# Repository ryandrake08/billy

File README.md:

# Smart Mouth Billy Bass LLM jokester

Billy is a Big Mouth Billy Bass novelty toy converted into an **offline, LAN-only** voice
jokester. An ESP32-S3 inside the fish captures speech, drives the motors, and plays back
audio; a separate GPU box does speech-to-text, LLM inference, and text-to-speech. There is no
internet dependency anywhere in the pipeline.

The fish's' persona, conversation history, text cleanup, and configuraion all live on the
backend, in an business-logic "shim" application in front of the LLM. The fish just captures
audio, makes three HTTP calls per turn, plays the reply, and animates the mouth/head/tail in
sync with it.

## Architecture

```
        FISH (ESP32-S3)                                BACKEND (LAN)
  ┌──────────────────────────┐                  ┌───────────────────────────┐
  │ mic → capture utterance  │─── utterance ───▶│ whisper.cpp        :8081  │
  │                          │◀───── text ──────│                           │
  |                          |                  |                           |    ┌─────────────────┐
  │ text → shim              │────── text ─────▶│ shim (persona,     :8000  │──▶ | llama.cpp :8080 |
  │                          │◀─── response ────│  history, text cleaning)  │    └─────────────────┘
  │                          │                  │                           │
  │ sentence → TTS           │──── sentence ───▶│ Kokoro             :8880  │
  │                          │◀──── audio ──────│                           │
  │ amp + motors             │                  └───────────────────────────┘
  └──────────────────────────┘
```

Three calls per conversational turn:

| Call | Target | Request → Response |
|---|---|---|
| STT | whisper.cpp `:8081`, direct | `POST /inference` (multipart wav, `response_format=verbose_json`, `language=auto`) → `{"text", "detected_language", ...}` |
| brain | shim `:8000` | `POST /v1/respond` `{session, text, language}` → SSE stream of `{"sentence", "voice"}` |
| TTS | Kokoro `:8880`, direct | `POST /v1/audio/speech` `{model, input, voice}` → wav bytes |

STT and TTS are dumb audio↔text transforms called **directly**; only the brain hop goes through
the shim, which is a text-only service that never touches audio. The shim streams sentences as
the LLM generates them, so the caller can synthesize and play sentence 1 while sentence 2 is
still being generated — this pipelining is what keeps time-to-first-audio low.

There are three implementations of this protocol, and they should be indentical: the reference clients
`src/client/billy_cli.py` (Python) and `src/cli/` (C), and the ESP32 firmware
(`src/firmware/main/net.c`). The CLIs exist to document the protocol the firmware has to match —
the C one doubles as a check on how much of the firmware's own protocol code (WAV header,
hand-rolled JSON parsing, SSE reassembly) is genuinely ESP-IDF-independent and portable to a
host build; it turned out to be all of it.

## Repository layout

| Path | What |
|---|---|
| `board/` | Custom PCB for the fish's electronics (KiCad). |
| `src/firmware/` | ESP32-S3 firmware (C, ESP-IDF). |
| `src/shim/` | Backend application-logic layer (Python/FastAPI). |
| `src/client/` | CLI reference client (Python) — a mic+speaker stand-in for the fish. |
| `src/cli/` | CLI reference client (C) — built against libcurl/PortAudio/soxr. |
| `src/tests/` | End-to-end integration test for the multi-language STT→shim→LLM pipeline. |

---

## `board/` — Custom PCB

KiCad project at `board/billy/`. Replaces the toy's stock control board with a single board
carrying the ESP32-S3, motor drivers, amp, buck regulator, and power-input protection,
designed to fit inside the original toy's chassis (~70×50mm).

| Part | Role |
|---|---|
| ESP32-S3-WROOM-1-N4R2 | Controller — WiFi, dual I²S, deep sleep |
| TDK ICS-43434 (I²S MEMS mic) | Microphone — mounted as a separate satellite board, off the main PCB, for acoustic placement |
| MAX98357A (I²S class-D amp) | Speaker drive |
| 2× TI DRV8833 (dual H-bridge) | 3 motor channels — mouth, head, tail (all spring-return, unidirectional) |
| DIODES AP63203 buck | 6V → 3.3V logic/audio rail |
| AOS AO3401A / AO3400A FETs (battery reverse-polarity protection, USB/motor-rail isolation pass FET, status LED + photocell/Vmotor-sense divider gating) | Power-input protection and deep-sleep peripheral gating |
| Analog Devices LTC4412 | Ideal-diode controller — motor rail vs. USB arbitration into the buck |
| MCC B5817W Schottky | Passive ideal diode — USB VBUS into the buck |
| 2× 5A slow-blow fuses | Battery and DC-jack input protection |

The KiCad schematic and PCB are authoritative for hardware connectivity and layout. Firmware
`board.h` mirrors the schematic's GPIO assignments and must stay synchronized with it.

**Workflow:**
```bash
open board/billy/billy.kicad_pro
kicad-cli sch erc --format json --severity-all -o erc.json board/billy/billy.kicad_sch
kicad-cli pcb drc --format json --severity-all --schematic-parity -o drc.json board/billy/billy.kicad_pcb
```

---

## `src/firmware/` — ESP32-S3 firmware

Captures speech, calls the backend for STT → LLM → TTS, plays the reply, and drives the
mouth/head/tail motors in sync with it. Targets `esp32s3` (tested with ESP-IDF v6.0.2).

### Layering

| Layer | Files | Responsibility |
|---|---|---|
| app | `main.c` | `app_main()` wires everything together; `runloop_task` runs the `IDLE→ACTIVATE→LISTEN→THINK→SPEAK→IDLE` state machine. |
| transport | `net.c/.h` | The fish↔backend contract described above — STT direct, brain hop through the shim, TTS direct. |
| device | `audio.c/.h`, `motors.c/.h`, `activation.c/.h`, `peripherals.c/.h` | Fish-specific setup and algorithms built on the HAL: I²S mic/amp + mouth lip-sync envelope; 2× DRV8833 motor choreography with `nFAULT` telemetry and deferred Vmotor capture; button/mode-switch/wake-word activation + deep sleep; WS2812 status LED + photocell/Vmotor-sense reads, all gated by one shared enable line. |
| HAL | `hal.c/.h` | Generic, pin-parameterized primitives (GPIO, ADC1, LED strip, PWM, I²S, deep sleep) with no fish-specific naming and no `board.h` dependency of its own. |

`board.h` is the firmware representation of the schematic pin map. `components/wakeword` is the on-device
wake-word detector (TensorFlow Lite Micro, ported from ESPHome's `micro_wake_word` component). See its own
`models/ATTRIBUTION.md` for training provenance.

### Build

```bash
source ~/.espressif/tools/activate_idf_v6.0.2.sh
cd src/firmware
export WIFI_SSID="your-2.4GHz-ssid" WIFI_PASSWORD="your-password" BACKEND_HOST="your-backend-hostname-or-ip"
idf.py set-target esp32s3      # once
idf.py build
idf.py -p <port> flash monitor
```
WiFi credentials and the backend host are build-environment variables injected as compile
definitions (`main/CMakeLists.txt`). Changing one needs `idf.py reconfigure`. `./clean.sh`
removes all generated build state.

### Debug

Step-debug with breakpoints over the S3's native USB-Serial-JTAG:
```bash
openocd -f board/esp32s3-builtin.cfg    # terminal 1
idf.py -p <port> gdb                    # terminal 2
```
The DevKitC-1 has two USB ports — flashing uses the UART/CP2102 port; OpenOCD needs the
separate native-USB port instead. The production board has a USB port and a three pin
header (TTL level) to one of the ESP32's built-in UARTs. Only use a USB-to-UART cable that
uses 3.3V with this header! In addition to the direct-to-UART header, the production board
has a two pin header for firmware flashing. Jumping the header during a reset causes the chip
to enter UART download (flashing) mode instead of booting normally from flash memory.
The UART/FLASH headers are intended to be a backup in case flashing over USB fails, and the
header can be left unpopulated if unused.

### Runtime behavior

`runloop_task` starts immediately on boot and idles waiting for activation; it does not block
on WiFi or the backend being reachable. Activation depends on the mode switch: **button mode**
(press-to-talk, deep-sleeps between turns) or **wake-word mode** (mic stays live, listens for
"hey billy"; a button press also works as a manual override). Flipping the switch mid-wait
preempts immediately. Runtime-tunable constants (VAD thresholds, mouth/tail timing, and HTTP
timeouts) are fetched from the shim's `/v1/config` every loop cycle rather than compiled
in, with compiled-in fallbacks if the shim is unreachable. Each capture's VAD threshold adapts
to the room's ambient noise level, measured during the pre-capture drain window, so a noisy
room still reads as silence once the user stops talking. The DRV8833 `nFAULT` line is logged but
does not gate motor commands because it asserts unreliably on the board; the drivers' independent
silicon overcurrent, thermal, and undervoltage protection remains active.

---

## `src/shim/` — backend application-logic layer

The brain layer in front of `llama.cpp`. Holds the application logic that has to live off the
fish for it to stay a thin client:

- **persona** / system prompt — edit `text.py`, reload;
- **conversation history / session state** — kept server-side, keyed by session id;
- **model quirks** — the `enable_thinking` request flag and `<think>`-block stripping;
- **markdown/emoji scrubbing** — the LLM still emits stray formatting that TTS would mangle;
- **sentence splitting + streaming** — emits clean sentences as they're ready so the caller can
  pipeline TTS for low first-audio latency;
- **per-language voice routing** (`text.py`'s `LANGUAGE_VOICES`) — English (`am_onyx`) plus
  Spanish, Brazilian Portuguese, Mandarin, Japanese, Hindi, and Italian, picked from the caller's
  detected language and overridable per sentence for an explicit switch mid-reply;
- **runtime firmware config** (`fish_config.py`) — tunable firmware constants served over
  `GET /v1/config`, so they can be retuned without a reflash.

### Protocol

| Call | Request | Response |
|---|---|---|
| `POST /v1/respond` | `{"session": "default", "text": "<user utterance>", "language": "english"}` | `text/event-stream`: one `data: {"sentence": ..., "voice": ...}` per spoken sentence, then `data: [DONE]` |
| `POST /v1/reset` | `{"session": "default"}` | `{"reset": "<session>"}` |
| `GET /v1/config` | — | Runtime firmware-tunable constants |
| `GET /health` | — | `{status, llm_url, llm_model, llm_reachable, sessions}` |

### Run

```bash
cd src/shim
python3 -m venv .venv && .venv/bin/pip install -r requirements.txt
.venv/bin/uvicorn billy_shim:app --host 0.0.0.0 --port 8000
```
Config via env: `BILLY_LLM_URL` (default `http://localhost:8080`), `BILLY_LLM_MODEL` (default
`Qwen3.5-9B`). Tests use plain asserts rather than pytest:

```bash
.venv/bin/python test_text.py
.venv/bin/python test_config.py
.venv/bin/python test_session.py
```

### Deploy

Shim program can live anywhere. Recommend using your OS's init system to start and manage it.

---

## `src/client/` — CLI reference client (Python)

A command-line stand-in for the fish: drives the full backend pipeline (record → STT → shim →
TTS → play) from any host with a mic and speaker.

### Run

```bash
cd src/client
python3 -m venv .venv && . .venv/bin/activate && pip install -r requirements.txt
./billy_cli.py --host <backend-host>     # ports 8000/8081/8880 derived from host
```
Press **Enter** to start talking, speak, press **Enter** to stop. `Ctrl-C` quits.

`--voice <kokoro-voice>` overrides the voice for the whole session (browse the list at
`http://<backend-host>:8880/web`); otherwise each sentence uses the shim's own per-sentence
choice. `--session <id>` sets the shim conversation id; `--shim-url`/`--stt-url`/`--tts-url`
override individual endpoints. Uses the system default audio devices.

`--input-wav <path>` skips the mic entirely: runs one turn on that WAV file's bytes (16 kHz mono,
same as the mic path itself records) and exits — for testing the same utterance repeatedly
without re-recording it by hand each time.

Each turn prints various latency measurements.

---

## `src/cli/` — CLI reference client (C)

A second, independent reference client for the same contract — same record → STT → shim → TTS →
play pipeline as the Python client, same flags, same latency breakdown, but built as a plain C
binary via CMake instead of a Python venv.

External dependencies (none of this is vendored): `libcurl` (HTTP, mirrors `httpx`), `portaudio`
(mic/speaker I/O, mirrors `sounddevice`), `soxr` (output resampling, same library the Python
`soxr` package binds to). On macOS via MacPorts: `port install curl portaudio soxr`.

### Build & run

```bash
cd src/cli
cmake -S . -B build && cmake --build build
./build/billy_cli --host <backend-host>     # ports 8000/8081/8880 derived from host
```
Press **Enter** to start talking, speak, press **Enter** to stop. `Ctrl-C` quits, same as the
Python client.

Same `--voice`/`--session`/`--shim-url`/`--stt-url`/`--tts-url` flags as the Python client, same
system-default audio devices. TTS audio is resampled to the output device's native rate in
software (soxr, `SOXR_HQ` quality).

---

## `src/tests/` — end-to-end integration test

Exercises the  STT→shim→LLM chain for every supported language. For each language, a
"golden" WAV asking Billy to repeat a fixed phrase is transcribed by real whisper.cpp, then sent
to a shim, checking the reply comes back in the right voice and language.

```bash
cd src/tests
python3 -m venv .venv && .venv/bin/pip install -r requirements.txt
./.venv/bin/python test_language_integration.py     # needs src/shim/.venv already set up
```

The golden WAVs in `golden/` are gitignored: `generate_golden.py` makes them with Microsoft's
free `edge-tts`. The test does this itself the first time golden/ is missing a file.

---

## Backend engines

Three off-the-shelf inference engines run on the backend GPU host alongside the shim, all under
systemd (`Restart=always`, enabled at boot):

| Service | Port | Model | GPU |
|---|---|---|---|
| llama.cpp | 8080 | Qwen3.5-9B, Q8_0, non-thinking mode | yes |
| whisper.cpp | 8081 | `large-v3` | yes |
| Kokoro (Kokoro-FastAPI) | 8880 | `am_onyx` + 6 other language voices (see `src/shim/`) | yes |

All three plus the shim are expected to fit resident in ~14GB of VRAM.

---

## License

Source code and documentation are licensed under [Apache License 2.0](LICENSE). The
trained wake-word model `src/firmware/components/wakeword/models/hey_billy.tflite` is
explicitly excluded; see [NOTICE](NOTICE) and its
[`ATTRIBUTION.md`](src/firmware/components/wakeword/models/ATTRIBUTION.md).

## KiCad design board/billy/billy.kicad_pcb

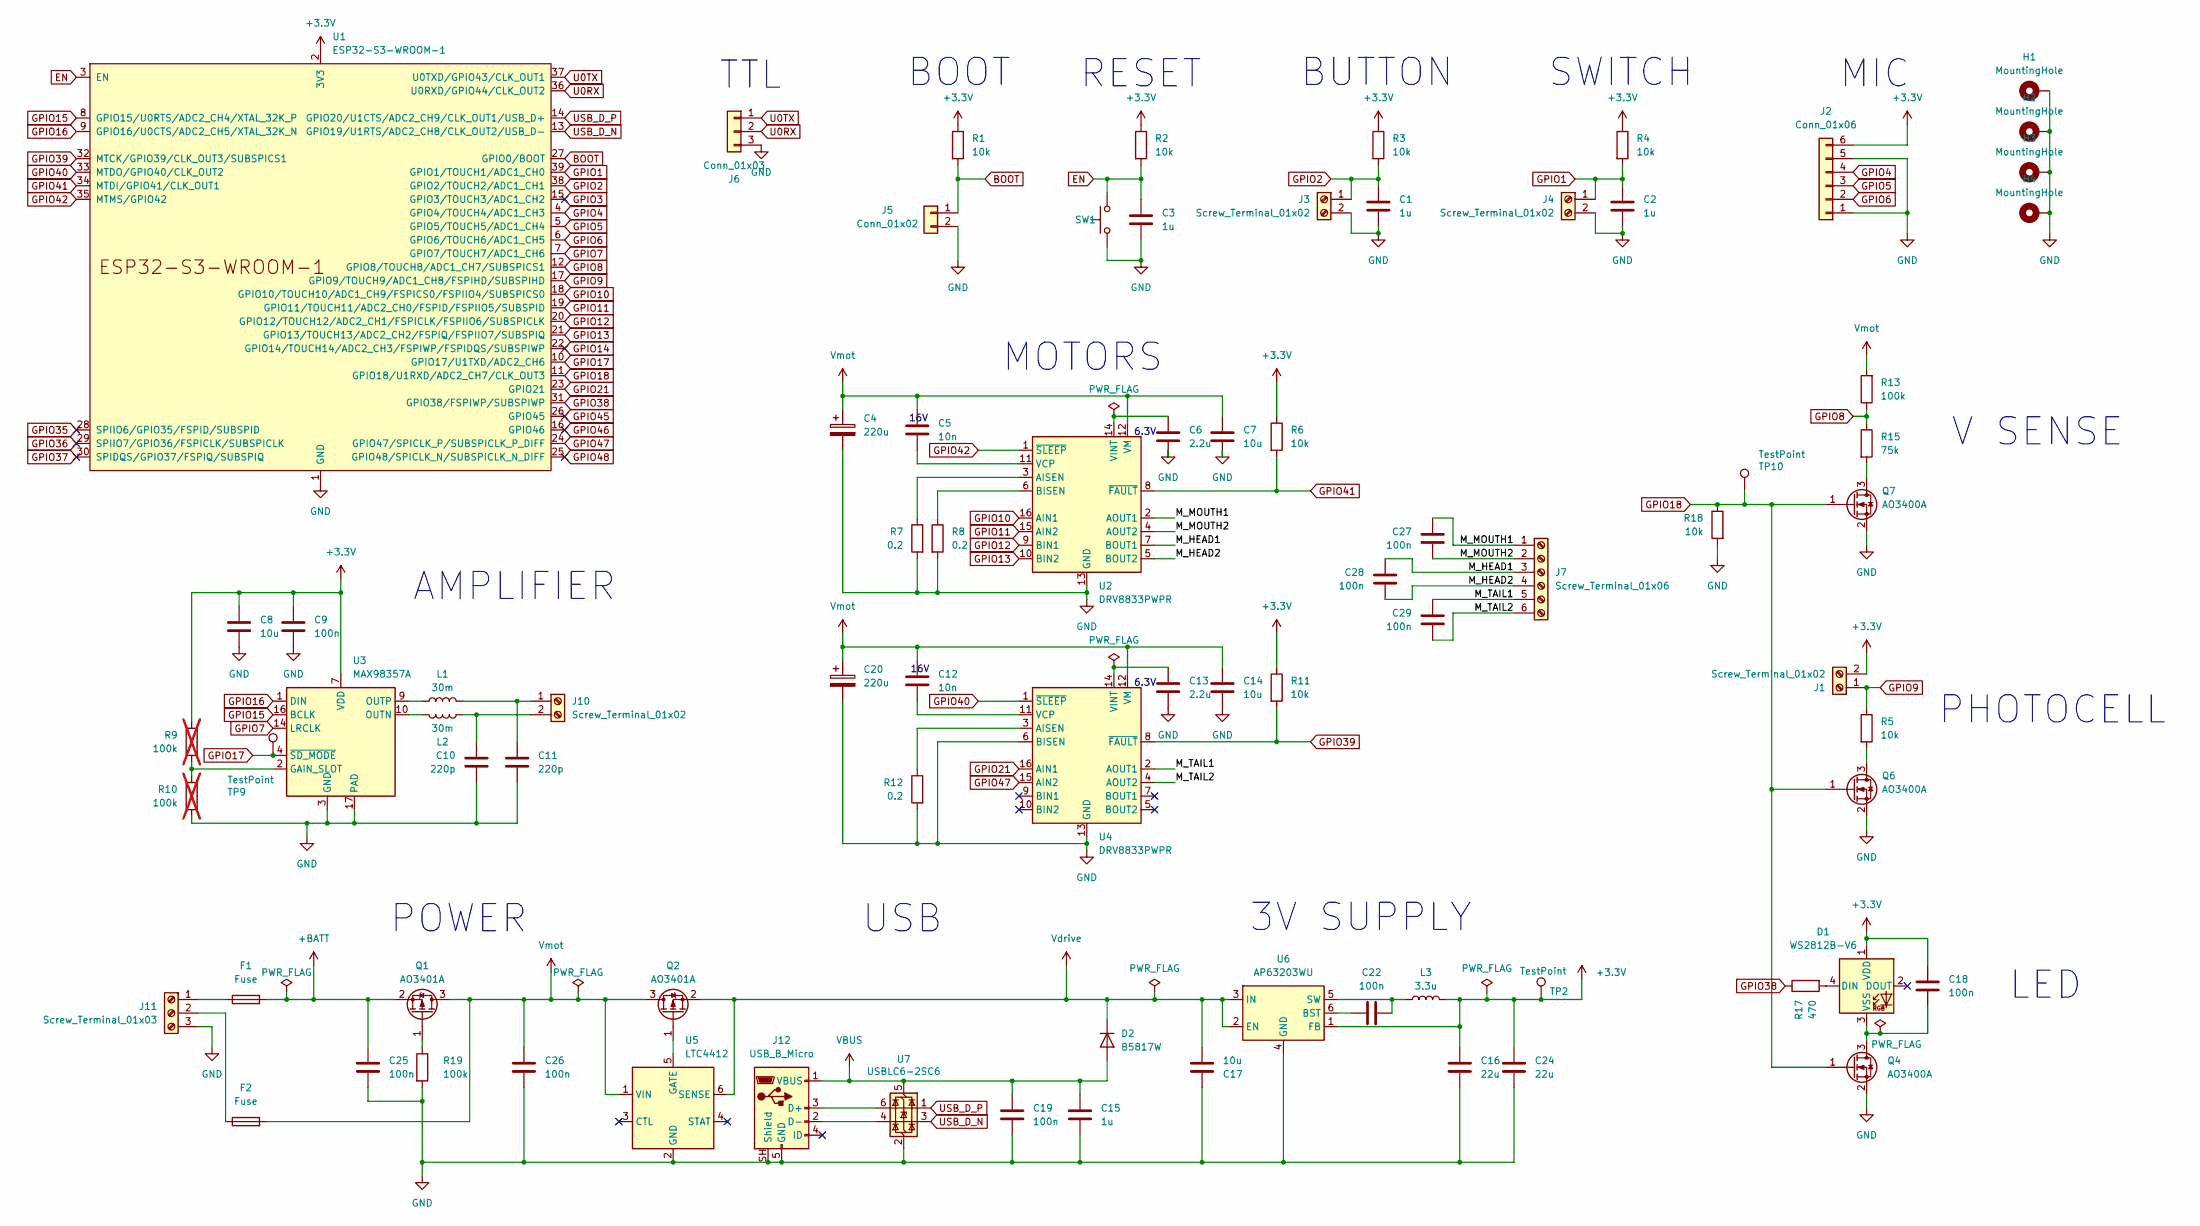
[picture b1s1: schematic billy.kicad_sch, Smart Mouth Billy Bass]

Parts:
C1, C2, C3, C15: 1u; C_0603_1608Metric; Mouser Part 187-CL10B105KP8NNNC; LCSC Part C52923
C4, C20: 220u; CP_Elec_6.3x5.9; Mouser Part 667-EEE-FT1C221AP; LCSC Part C401766
C5, C12: 10n; C_0603_1608Metric; Mouser Part 187-CL05B103KB5NNNC; LCSC Part C15195
C6, C13: 2.2u; C_0603_1608Metric; Mouser Part 187-CL10A225KP8NNNC; LCSC Part C23630
C7, C8, C14: 10u; C_0603_1608Metric; Mouser Part 187-CL10A106KP8NNND; LCSC Part C19702
C9, C18, C19, C22, C25, C26, C27, C28, C29: 100n; C_0603_1608Metric; Mouser Part 187-CL10B104JB8NNNC; LCSC Part C1525
C10, C11: 220p; C_0603_1608Metric; Mouser Part 187-CL10B221KB8NNNC; LCSC Part C1530
C16, C24: 22u; C_1206_3216Metric; Mouser Part 187-CL31B226KPHNNNE; LCSC Part C45783
C17: 10u; C_1206_3216Metric; Mouser Part 187-CL31B106KLHNNNE; LCSC Part C45783
D1: WS2812B-V6; LED_WS2812B_PLCC4_5.0x5.0mm_P3.2mm; LCSC Part C52941391
D2: B5817W; D_SOD-323; Mouser Part 833-B5817W-TP; DigiKey Part B5817WS-TPMSCT-ND
F1, F2: Fuse; Fuse_Littelfuse-NANO2-451_453; Mouser Part 576-0454005.MR; LCSC Part C206917
H1, H2, H3, H4: MountingHole; MountingHole_3.2mm_M3_ISO7380_Pad
J1, J3, J4, J10: Screw_Terminal_01x02; TerminalBlock_Xinya_XY308-2.54-2P_1x02_P2.54mm_Horizontal; Mouser Part 651-1725656; LCSC Part C918120
J2: Conn_01x06; PinHeader_1x06_P2.54mm_Horizontal; Mouser Part 710-61300611021; LCSC Part C492414
J5: Conn_01x02; PinHeader_1x02_P2.54mm_Vertical; Mouser Part 710-61300211121; LCSC Part C492401
J6: Conn_01x03; PinHeader_1x03_P2.54mm_Vertical; Mouser Part 710-61300311121; LCSC Part C2937625
J7: Screw_Terminal_01x06; TerminalBlock_Xinya_XY308-2.54-6P_1x06_P2.54mm_Horizontal; Mouser Part 651-1725698; LCSC Part C918124
J11: Screw_Terminal_01x03; TerminalBlock_Xinya_XY308-2.54-3P_1x03_P2.54mm_Horizontal; Mouser Part 651-1725669; LCSC Part C918121
J12: USB_B_Micro; USB_Micro-B_Amphenol_10118194-0001LF_Horizontal; Mouser Part 649-10118194-0001LF; LCSC Part C132563
L1, L2: 30m; L_0603_1608Metric; Mouser Part 81-BLM18KG121TN1D; LCSC Part C14709
L3: 3.3u; L_APV_ANR4030; Mouser Part 739-TYA40203R3M-10; DigiKey Part 240-TYA40203R3M-10CT-ND
Q1, Q2: AO3401A; SOT-23; LCSC Part C15127
Q4, Q6, Q7: AO3400A; SOT-23; LCSC Part C20917
R1, R2, R3, R4, R5, R6, R11, R18: 10k; R_0603_1608Metric; Mouser Part 708-RMCF0603FT10K0; LCSC Part C25804
R7, R8, R12: 0.2; R_1206_3216Metric; Mouser Part 708-CSR1206FKR200; LCSC Part C473037
R9, R10: 100k; R_0603_1608Metric; Mouser Part 708-RMCF0603FT100K; LCSC Part C25803; not fitted
R13, R19: 100k; R_0603_1608Metric; Mouser Part 708-RMCF0603FT100K; LCSC Part C25803
R15: 75k; R_0603_1608Metric; Mouser Part 708-RMCF0603FT75K0; DigiKey Part RMCF0603FT75K0CT-ND
R17: 470; R_0603_1608Metric; Mouser Part 708-RMCF0603FT470R; LCSC Part C23179
SW1: TS-1088-AR02016; SW_SPST_TS-1088-xR020; Mouser Part 688-SKRKAG; LCSC Part C720477
TP2, TP9, TP10: TestPoint; TestPoint_Pad_1.0x1.0mm
U1: ESP32-S3-WROOM-1; Mouser Part 356-ESP32S3WROM1N4R2; LCSC Part C2913203
U2, U4: DRV8833PWPR; HTSSOP-16-1EP_4.4x5mm_P0.65mm_EP3.4x5mm; Mouser Part 595-DRV8833PWPR; LCSC Part C50506
U3: MAX98357A; TQFN-16-1EP_3x3mm_P0.5mm_EP1.23x1.23mm; Mouser Part 700-MAX98357AETE+T; LCSC Part C910544
U5: LTC4412; TSOT-23-6; Mouser Part 584-LTC4412ES6TRMPBF; DigiKey Part 505-LTC4412ES6#TRMPBFCT-ND
U6: AP63203WU; TSOT-23-6; Mouser Part 621-AP63203QWU-7; LCSC Part C780769
U7: USBLC6-2SC6; SOT-23-6; Mouser Part 511-USBLC6-2SC6; LCSC Part C7519

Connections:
+3.3V: C8.1, C9.1, C16.1, C18.1, C24.1, D1.1 (VDD), J1.2, J2.6, L3.2, R1.1, R2.1, R3.1, R4.1, R6.1, R9.1, R11.1, TP2.1 (1_1), U1.2 (3V3), U3.7 (VDD), U3.8 (VDD), U6.1 (FB)
+BATT: C25.1, F1.2, Q1.2 (S)
/M_HEAD1: C28.1, J7.3, U2.7 (BOUT1)
/M_HEAD2: C28.2, J7.4, U2.5 (BOUT2)
/M_MOUTH1: C27.1, J7.1, U2.2 (AOUT1)
/M_MOUTH2: C27.2, J7.2, U2.4 (AOUT2)
/M_TAIL1: C29.2, J7.5, U4.2 (AOUT1)
/M_TAIL2: C29.1, J7.6, U4.4 (AOUT2)
BOOT: J5.1, R1.2, U1.27 (GPIO0/BOOT)
EN: C3.1, R2.2, SW1.2, U1.3 (EN)
GND: C1.2, C2.2, C3.2, C4.2, C6.2, C7.2, C8.2, C9.2, C10.2, C11.2, C13.2, C14.2, C15.2, C16.2, C17.2, C19.2, C20.2, C24.2, C25.2, C26.2, H1.1 (1_1), H2.1 (1_1), H3.1 (1_1), H4.1 (1_1), J2.1, J2.5, J3.2, J4.2, J5.2, J6.3, J11.3, J12.5 (GND), J12.SH (Shield), Q4.2 (S), Q6.2 (S), Q7.2 (S), R7.2, R8.2, R10.2, R12.2, R18.2, R19.2, SW1.1, U1.1 (GND), U1.40 (GND), U1.41 (GND), U2.13 (GND), U2.17 (GND), U3.3 (GND), U3.11 (GND), U3.15 (GND), U3.17 (PAD), U4.6 (BISEN), U4.13 (GND), U4.17 (GND), U5.2 (GND), U6.4 (GND), U7.2 (GND)
GPIO1: C2.1, J4.1, R4.2, U1.39 (GPIO1/TOUCH1/ADC1_CH0)
GPIO2: C1.1, J3.1, R3.2, U1.38 (GPIO2/TOUCH2/ADC1_CH1)
GPIO3: U1.15 (GPIO3/TOUCH3/ADC1_CH2)
GPIO4: J2.4, U1.4 (GPIO4/TOUCH4/ADC1_CH3)
GPIO5: J2.3, U1.5 (GPIO5/TOUCH5/ADC1_CH4)
GPIO6: J2.2, U1.6 (GPIO6/TOUCH6/ADC1_CH5)
GPIO7: U1.7 (GPIO7/TOUCH7/ADC1_CH6), U3.14 (LRCLK)
GPIO8: R13.1, R15.1, U1.12 (GPIO8/TOUCH8/ADC1_CH7/SUBSPICS1)
GPIO9: J1.1, R5.1, U1.17 (GPIO9/TOUCH9/ADC1_CH8/FSPIHD/SUBSPIHD)
GPIO10: U1.18 (GPIO10/TOUCH10/ADC1_CH9/FSPICS0/FSPIIO4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), U2.16 (AIN1)
GPIO11: U1.19 (GPIO11/TOUCH11/ADC2_CH0/FSPID/FSPIIO5/S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), U2.15 (AIN2)
GPIO12: U1.20 (GPIO12/TOUCH12/ADC2_CH1/FSPICLK/FSPIIO6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), U2.9 (BIN1)
GPIO13: U1.21 (GPIO13/TOUCH13/ADC2_CH2/FSPIQ/FSPIIO7/S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), U2.10 (BIN2)
GPIO14: U1.22 (GPIO14/TOUCH14/ADC2_CH3/FSPIWP/FSPIDQS/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)
GPIO15: U1.8 (GPIO15/U0RTS/ADC2_CH4/XTAL_32K_P), U3.16 (BCLK)
GPIO16: U1.9 (GPIO16/U0CTS/ADC2_CH5/XTAL_32K_N), U3.1 (DIN)
GPIO17: TP9.1 (1_1), U1.10 (GPIO17/U1TXD/ADC2_CH6), U3.4 (~SD_MODE)
GPIO18: Q4.1 (G), Q6.1 (G), Q7.1 (G), R18.1, TP10.1 (1_1), U1.11 (GPIO18/U1RXD/ADC2_CH7/CLK_OUT3)
GPIO21: U1.23 (GPIO21), U4.16 (AIN1)
GPIO35: U1.28 (SPIIO6/GPIO35/FSPID/SUBSPID)
GPIO36: U1.29 (SPIIO7/GPIO36/FSPICLK/SUBSPICLK)
GPIO37: U1.30 (SPIDQS/GPIO37/FSPIQ/SUBSPIQ)
GPIO38: R17.1, U1.31 (GPIO38/FSPIWP/SUBSPIWP)
GPIO39: R11.2, U1.32 (MTCK/GPIO39/CLK_OUT3/SUBSPICS1), U4.8 (~FAULT)
GPIO40: U1.33 (MTDO/GPIO40/CLK_OUT2), U4.1 (~SLEEP)
GPIO41: R6.2, U1.34 (MTDI/GPIO41/CLK_OUT1), U2.8 (~FAULT)
GPIO42: U1.35 (MTMS/GPIO42), U2.1 (~SLEEP)
GPIO45: U1.26 (GPIO45)
GPIO46: U1.16 (GPIO46)
GPIO47: U1.24 (GPIO47/SPICLK_P/SUBSPICLK_P_DIFF), U4.15 (AIN2)
GPIO48: U1.25 (GPIO48/SPICLK_N/SUBSPICLK_N_DIFF)
unnamed: D1.4 (DIN), R17.2
unnamed: C18.2, D1.3 (VSS), Q4.3 (D)
unnamed: C11.1, J10.1, L1.2
unnamed: C10.1, J10.2, L2.1
unnamed: F1.1, J11.1
unnamed: F2.1, J11.2
unnamed: J12.3 (D+), U7.6 (I/O1)
unnamed: J12.2 (D-), U7.4 (I/O2)
unnamed: Q1.1 (G), R19.1
unnamed: Q2.1 (G), U5.5 (GATE)
unnamed: Q6.3 (D), R5.2
unnamed: Q7.3 (D), R15.2
unnamed: R7.1, U2.3 (AISEN)
unnamed: R8.1, U2.6 (BISEN)
unnamed: C5.2, U2.11 (VCP)
unnamed: C6.1, U2.14 (VINT)
unnamed: R9.2, R10.1, U3.2 (GAIN_SLOT)
unnamed: L2.2, U3.10 (OUTN)
unnamed: L1.1, U3.9 (OUTP)
unnamed: R12.1, U4.3 (AISEN)
unnamed: C12.2, U4.11 (VCP)
unnamed: C13.1, U4.14 (VINT)
unnamed: C22.1, U6.6 (BST)
unnamed: C22.2, L3.1, U6.5 (SW)
U0RX: J6.2, U1.36 (U0RXD/GPIO44/CLK_OUT2)
U0TX: J6.1, U1.37 (U0TXD/GPIO43/CLK_OUT1)
USB_D_N: U1.13 (GPIO19/U1RTS/ADC2_CH8/CLK_OUT2/USB_D-), U7.3 (I/O2)
USB_D_P: U1.14 (GPIO20/U1CTS/ADC2_CH9/CLK_OUT1/USB_D+), U7.1 (I/O1)
VBUS: C15.1, C19.1, D2.2 (A), J12.1 (VBUS), U7.5 (VBUS)
Vdrive: C17.1, D2.1 (K), Q2.2 (S), U5.6 (SENSE), U6.2 (EN), U6.3 (IN)
Vmot: C4.1, C5.1, C7.1, C12.1, C14.1, C20.1, C26.1, F2.2, Q1.3 (D), Q2.3 (D), R13.2, U2.12 (VM), U4.12 (VM), U5.1 (VIN)

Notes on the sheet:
SWITCH
16V
LED
AMPLIFIER
3V SUPPLY
USB
TTL
BOOT
RESET
MIC
POWER
PHOTOCELL
V SENSE
BUTTON
6.3V
MOTORS

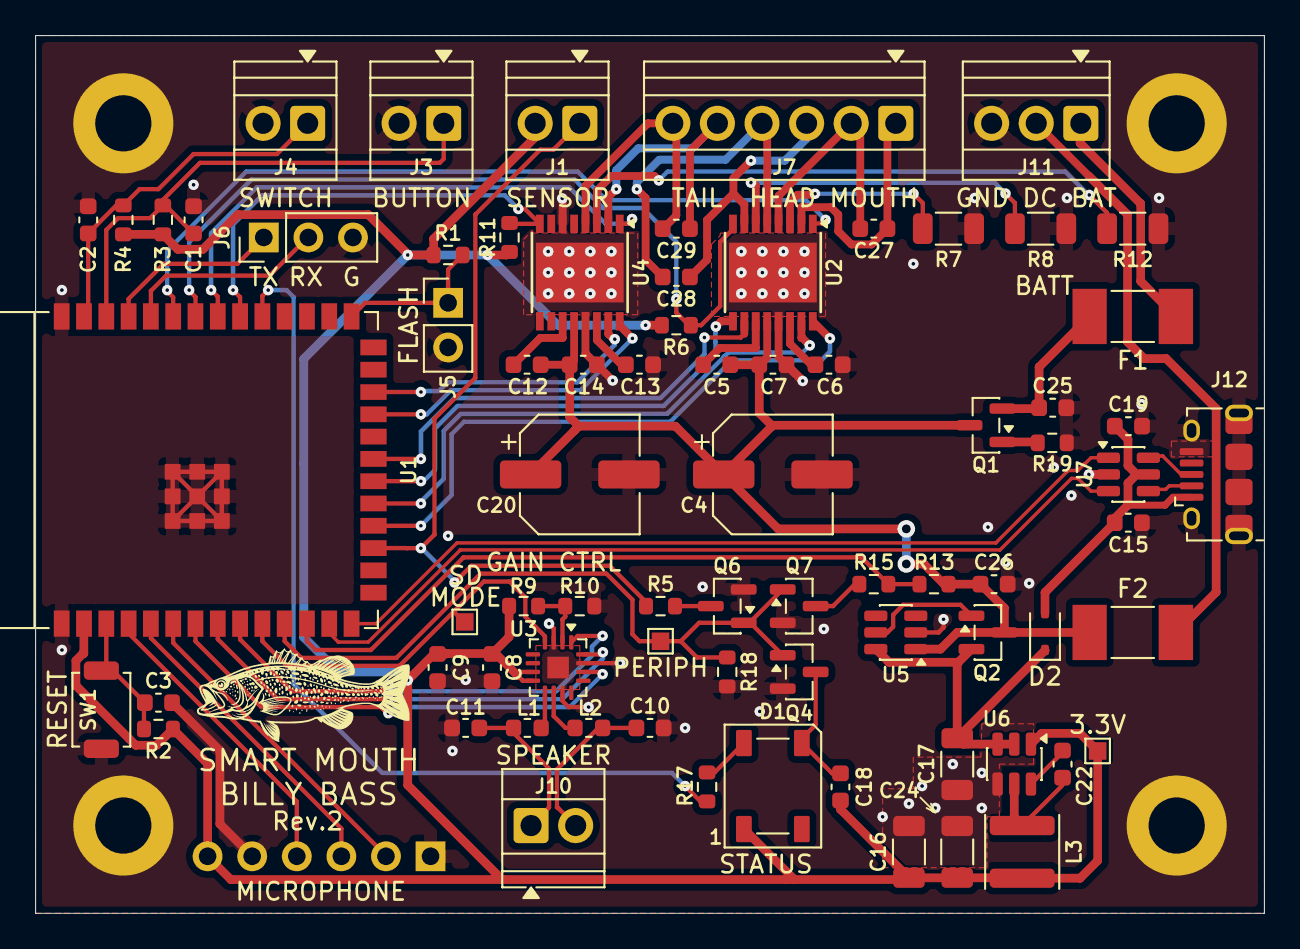
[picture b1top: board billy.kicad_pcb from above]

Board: 2 copper layers, 70.0 x 50.0 mm, 81 parts (1 on the bottom side), 65 nets.
